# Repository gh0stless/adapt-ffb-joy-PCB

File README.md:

# adapt-ffb-joy-PCB
an PCB and 3D housing for adapt-ffb-joy the USB adapter for Microsoft Sidewinder Pro

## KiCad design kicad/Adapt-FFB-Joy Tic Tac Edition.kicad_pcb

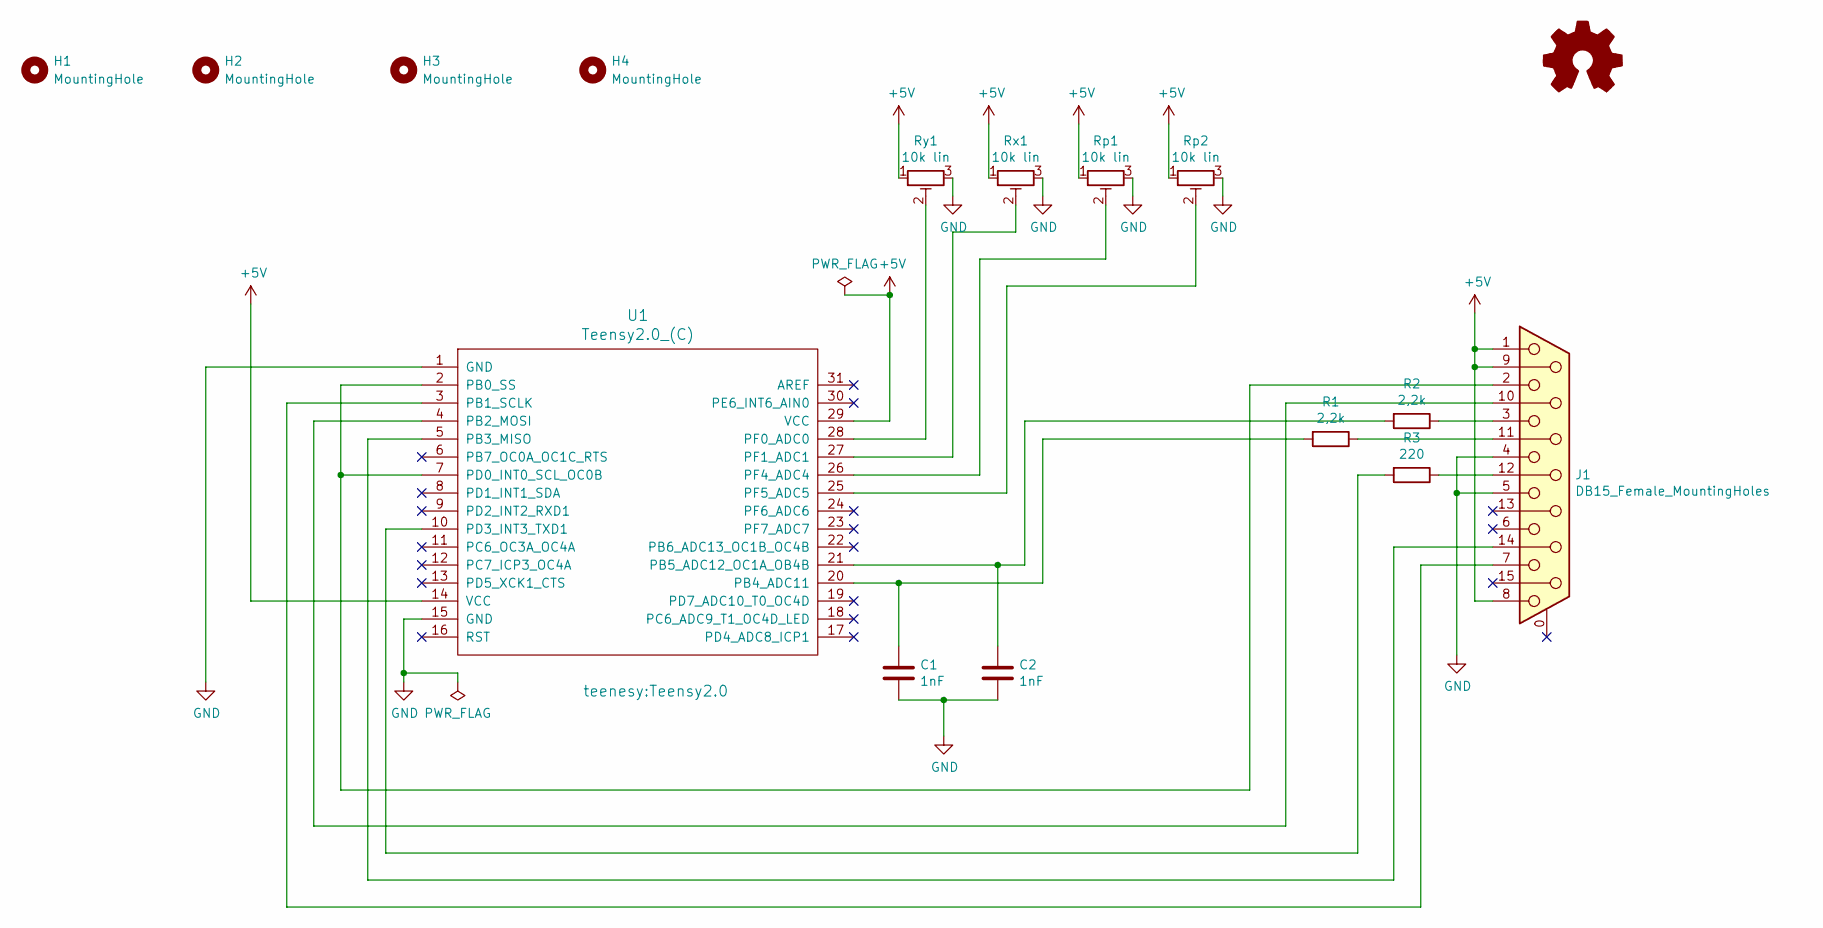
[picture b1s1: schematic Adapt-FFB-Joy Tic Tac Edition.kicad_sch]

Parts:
C1, C2: 1nF; C_Disc_D3.0mm_W2.0mm_P2.50mm
H1, H2, H3, H4: MountingHole; MountingHole_3.2mm_M3
J1: DB15_Female_MountingHoles; DSUB-15_Female_Horizontal_P2.77x2.84mm_EdgePinOffset4.94mm_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
R1, R2: 2,2k; R_Axial_DIN0207_L6.3mm_D2.5mm_P10.16mm_Horizontal
R3: 220; R_Axial_DIN0207_L6.3mm_D2.5mm_P10.16mm_Horizontal
Rp1, Rp2: 10k lin; PinHeader_1x03_P2.54mm_Vertical
Rx1: 10k lin; PinHeader_1x03_P2.54mm_Vertical
Ry1: 10k lin; PinHeader_1x03_P2.54mm_Vertical
U1: Teensy2.0_(C); Teensy2.0

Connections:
+5V: J1.1, J1.8, J1.9, Rp1.1, Rp2.1, Rx1.1, Ry1.1, U1.14 (VCC), U1.29 (VCC)
GND: C1.2, C2.2, J1.4, J1.5, Rp1.3, Rp2.3, Rx1.3, Ry1.3, U1.1 (GND), U1.15 (GND)
unnamed: J1.10, U1.4 (PB2_MOSI)
unnamed: J1.12, R3.1
unnamed: J1.14, U1.5 (PB3_MISO)
unnamed: J1.11 (P111), R1.1
unnamed: J1.3, R2.1
unnamed: J1.2, U1.2 (PB0_SS), U1.7 (PD0_INT0_SCL_OC0B)
unnamed: J1.7, U1.3 (PB1_SCLK)
unnamed: C1.1, R1.2, U1.20 (PB4_ADC11)
unnamed: C2.1, R2.2, U1.21 (PB5_ADC12_OC1A_OB4B)
unnamed: R3.2, U1.10 (PD3_INT3_TXD1)
unnamed: Ry1.2, U1.28 (PF0_ADC0)
unnamed: Rx1.2, U1.27 (PF1_ADC1)
unnamed: Rp1.2, U1.26 (PF4_ADC4)
unnamed: Rp2.2, U1.25 (PF5_ADC5)

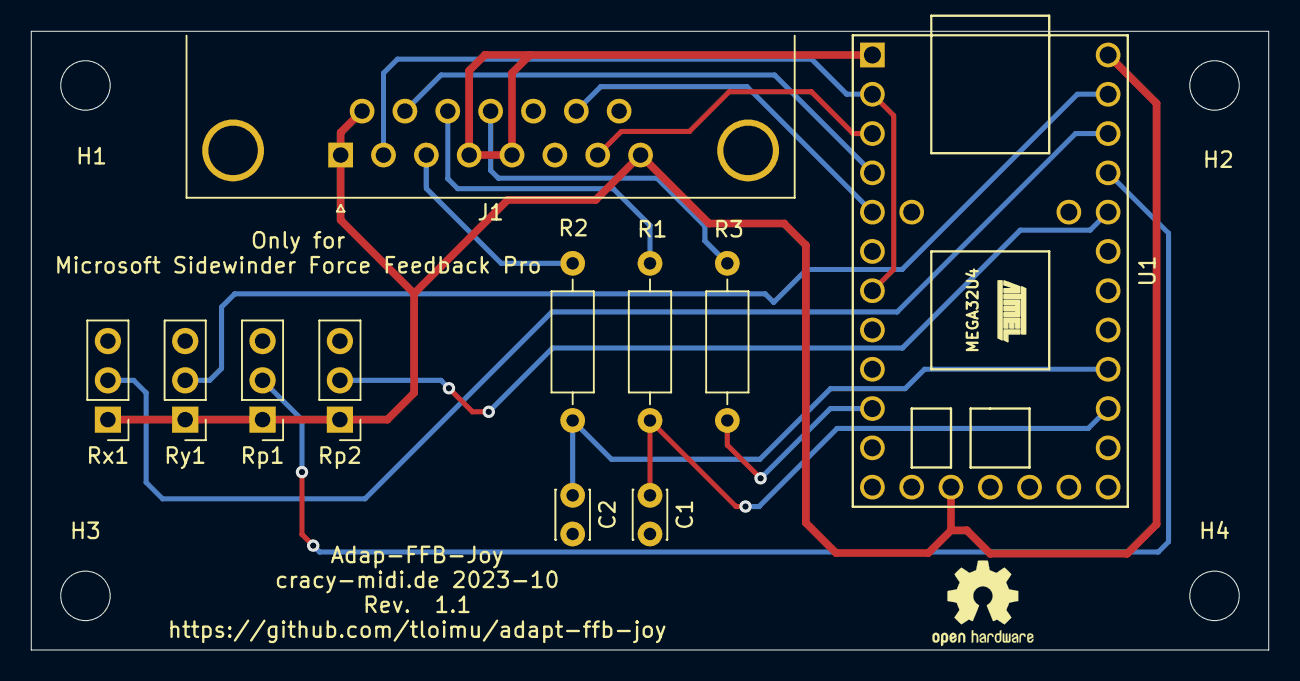
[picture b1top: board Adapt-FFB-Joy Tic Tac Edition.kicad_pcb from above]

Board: 2 copper layers, 80.0 x 40.0 mm, 15 parts (0 on the bottom side), 16 nets.

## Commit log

2023-10-18 initial
